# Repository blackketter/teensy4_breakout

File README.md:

A breakout board for the PJRC.com Teensy 4.0 board that is soldered directly to the bottom of the Teensy board via castellated solder points.

Note:  I've decided to not use this.  Check out [this newer version](https://github.com/blackketter/teensy4_header_breakout) which uses more common 0.1" headers.

Designed in KiCad.

Expands to 2 rows of .05" headers or further castellated solder points.

One advantage of this is that if the breakout board top is soldered directly
to the bottom of the host board, the Teensy can be flush with the main board via a cutout.

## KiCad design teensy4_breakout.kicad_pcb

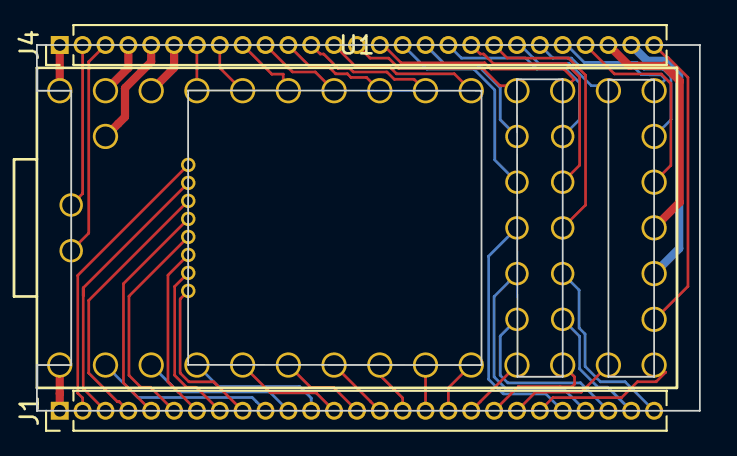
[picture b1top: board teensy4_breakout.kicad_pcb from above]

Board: 2 copper layers, 36.8 x 20.3 mm, 3 parts (0 on the bottom side), 54 nets.

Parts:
J1: Edge A; PinHeader_1x27_P1.27mm_Vertical
J4: Edge B; PinHeader_1x27_P1.27mm_Vertical
U1: Teensy4.0; Teensy40_SMT

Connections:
/0: J1.10, U1.2
/1: J1.11, U1.3
/2: J1.12, U1.4
/3: J1.13, U1.5
/3V3_1: J4.26, U1.16
/3V3_2: J1.6, U1.49
/3V3_3: J4.6, U1.31
/4: J1.14, U1.6
/5: J1.15, U1.7
/6: J1.16, U1.8
/7: J1.17, U1.9
/8: J1.18, U1.10
/9: J1.19, U1.11
/10: J1.20, U1.12
/11: J1.21, U1.13
/12: J1.22, U1.14
/13: J4.22, U1.20
/14: J4.21, U1.21
/15: J4.15, U1.22
/16: J4.14, U1.23
/17: J4.13, U1.24
/18: J4.12, U1.25
/19: J4.11, U1.26
/20: J4.10, U1.27
/21: J4.9, U1.28
/22: J4.8, U1.29
/23: J4.7, U1.30
/24: J4.18, U1.35
/25: J4.17, U1.36
/26: J4.19, U1.37
/27: J4.16, U1.38
/28: J4.20, U1.39
/29: J1.23, U1.40
/30: J1.27, U1.41
/31: J1.24, U1.42
/32: J1.26, U1.43
/33: J1.25, U1.44
/CLK: J1.5, U1.48
/CMD: J1.7, U1.50
/D+: J4.3, U1.54
/D-: J4.2, U1.53
/DAT0: J1.3, U1.46
/DAT1: J1.2, U1.45
/DAT2: J1.9, U1.52
/DAT3: J1.8, U1.51
/GND_1: J1.1, U1.1
/GND_2: J4.4, U1.32
/GND_3: J1.4, U1.47
/GND_4: J4.25, U1.17
/ON_OFF: J4.23, U1.19
/PROGRAM: J4.24, U1.18
/VBAT: J4.27, U1.15
/VIN: J4.1, U1.33
/VUSB: J4.5, U1.34

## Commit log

2019-08-17 First pass, ordered from OSHPark
2019-08-17 Add README
2019-08-17 Add rescue.lib file
2019-08-17 Minor update to README
2019-08-18 Move outside edges to castellate the 0.05" header pins to facilitate direct soldering to board. Pins can still be used, but a jig is required to solder them.
2019-08-18 Add an image
2019-09-16 Retiring
